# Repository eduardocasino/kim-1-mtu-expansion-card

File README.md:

# KIM-1 Expansion Board for MTU Cards

## About

Welcome to my KIM-1 Expansion Board for MTU cards repository.

This board follows the MTU standard for the KIM-1 expansion bus and enables to connect up to five cards, like the [K-1008](https://github.com/eduardocasino/k-1008-visable-memory-card-replica). Additionally, all signals of the KIM-1 are replicated on an edge connector to allow further expansions and also on a pin header for easy breadboarding.

The MTU bus connects 1 to 1 to the KIM-1 expansion connector with the exception of pins 2,3, 16, 17, 18, 19, 20 and X, because MTU boards use some of these pins for power and expanded 18 bit address bus (See page 33 of the [MTU Fall 1980 6502 Peripherals and Software catalog](http://retro.hansotten.nl/uploads/files/MTU-fall-1980.pdf)) Two pin connectors have to be wired to pins J (K7) and K (DECODE ENABLE) of the KIM-1 application connector.

Like in the original MTU's bus motherboard, a five screw terminal block provides power connectios for both the KIM-1 (GND, +5V and +12V regulated) and the expansion boards (+7.5V and +16V unregulated). Also as in the original, the +12V terminal is not really connected to anything.

This is how an example setup with one K-1008 board would look like:

The board has been built and tested with my [KIM-1](https://github.com/eduardocasino/kim-1) and [K-1008](https://github.com/eduardocasino/k-1008-visable-memory-card-replica) replicas.

## Licensing

This is a personal project that I am sharing in case it is of interest to any retrocomputing enthusiast and all the information in this repository is provided "as is", without warranty of any kind. I am not liable for any damages that may occur, whether it be to individuals, objects, KIM-1 computers, kittens or any other pets.

This work is licensed under a [Creative Commons Attribution-ShareAlike 4.0 International License](http://creativecommons.org/licenses/by-sa/4.0/).

See the LICENSE.md file for details.

## Changelog
#### 19/11/2023
* License change to a less restrictive one.
#### 11/11/2023
* Fix solder mask for connectors. For real this time. Damn.
#### 04/08/2023
* Fix solder mask for connectors

## Acknowledgements

* Hans Otten and his [Retro Computing blog](http://retro.hansotten.nl/). Documentation of MTU's line of hardware expansions for the KIM-1

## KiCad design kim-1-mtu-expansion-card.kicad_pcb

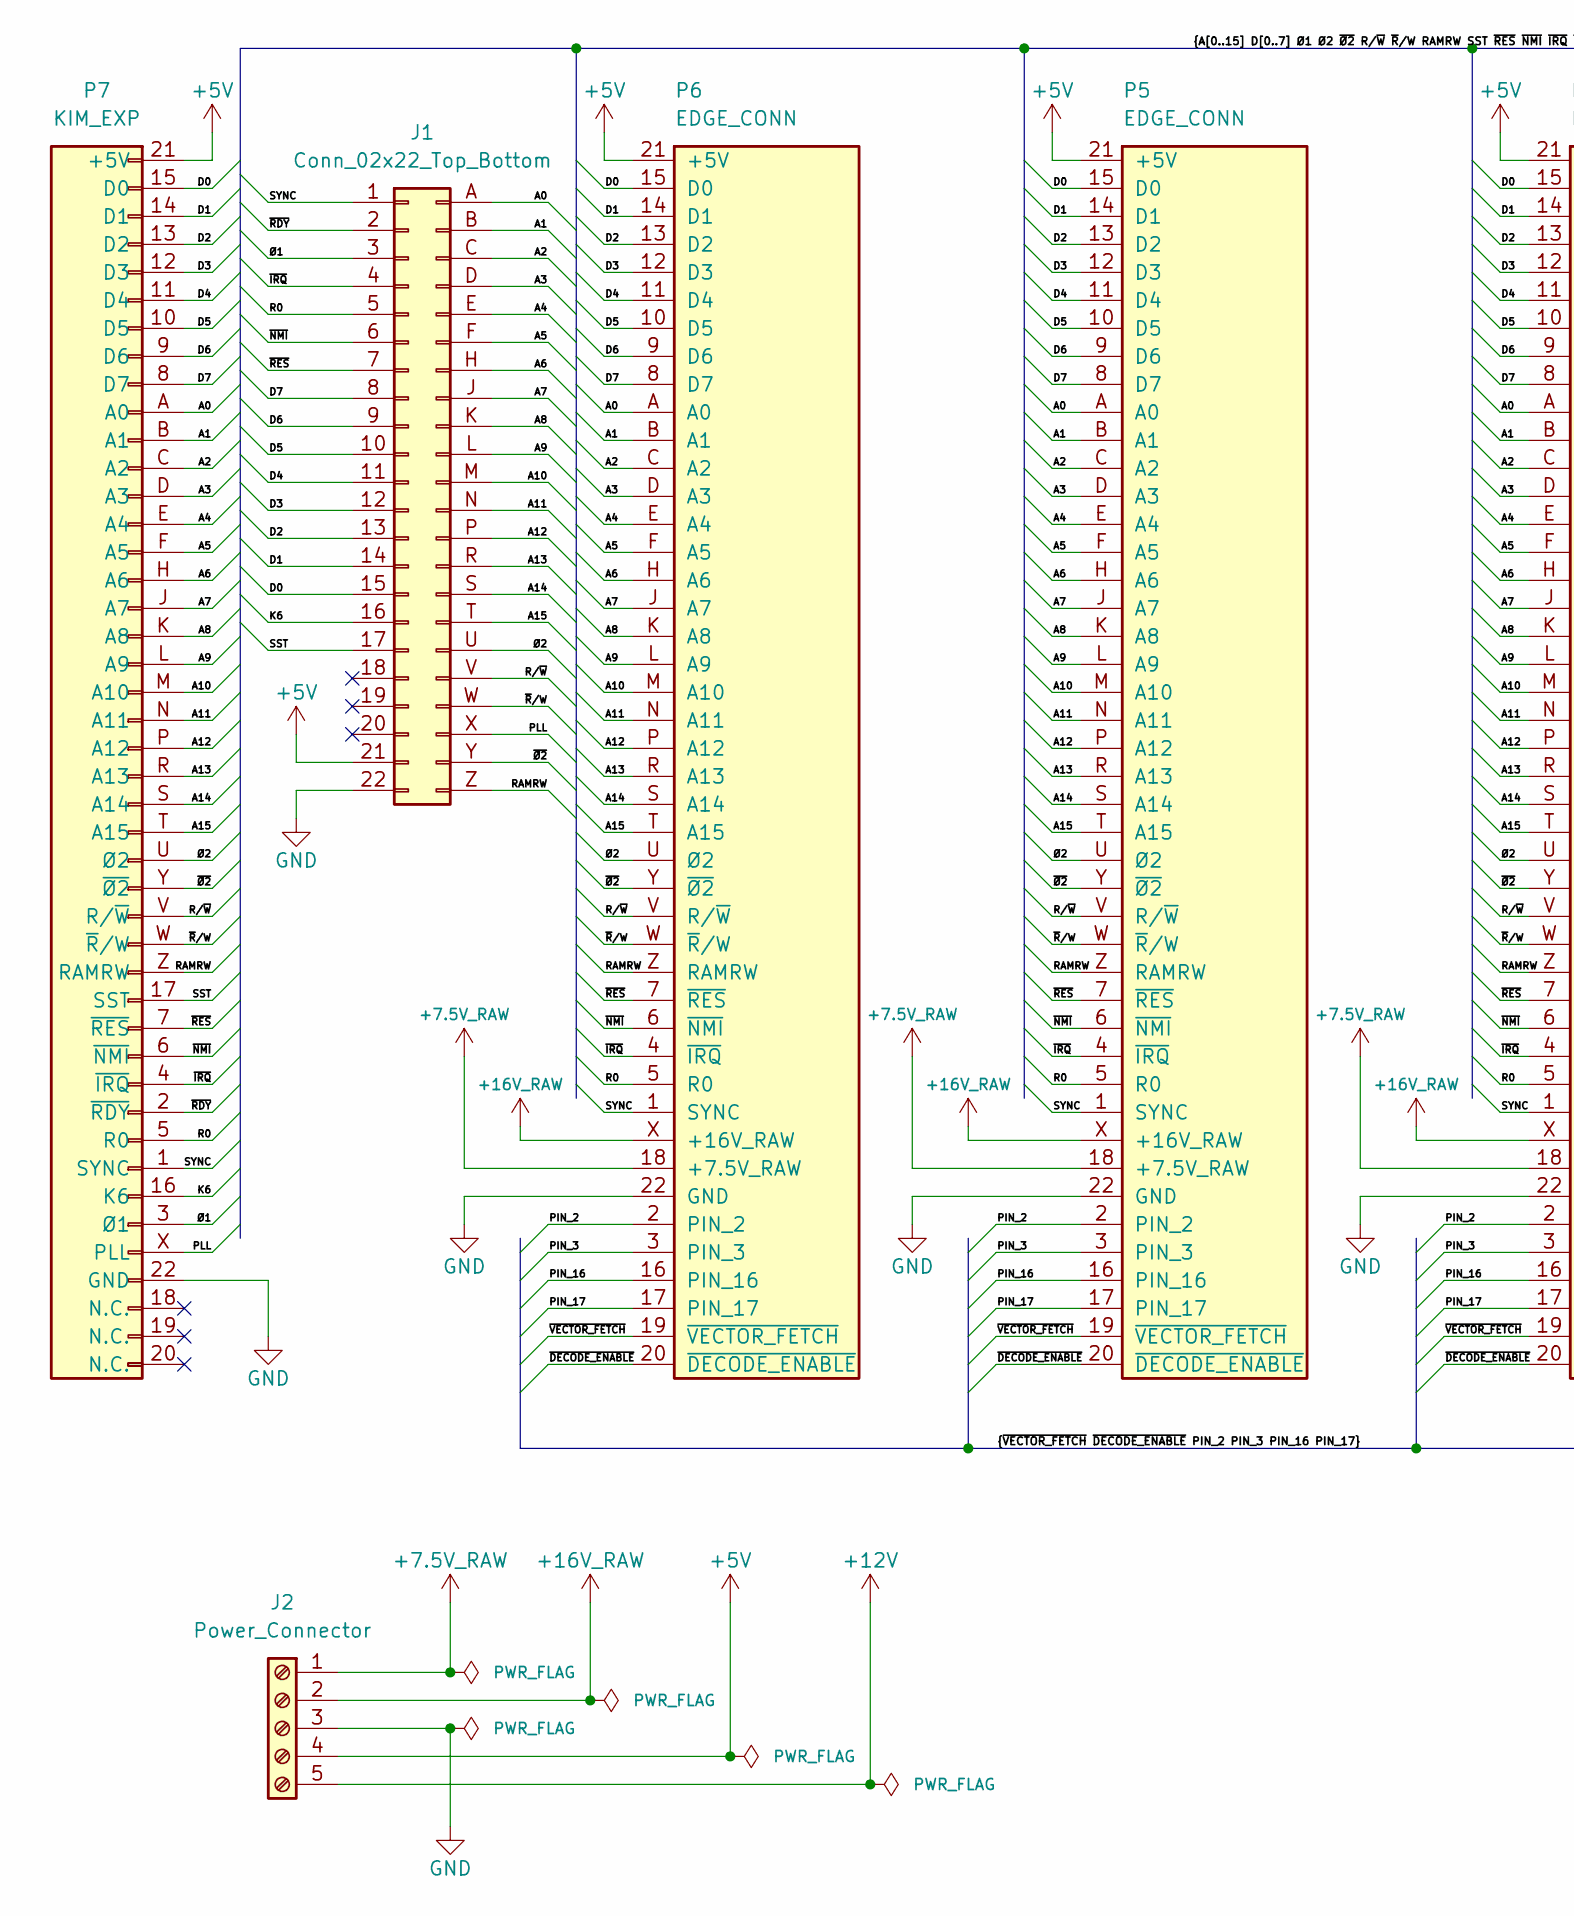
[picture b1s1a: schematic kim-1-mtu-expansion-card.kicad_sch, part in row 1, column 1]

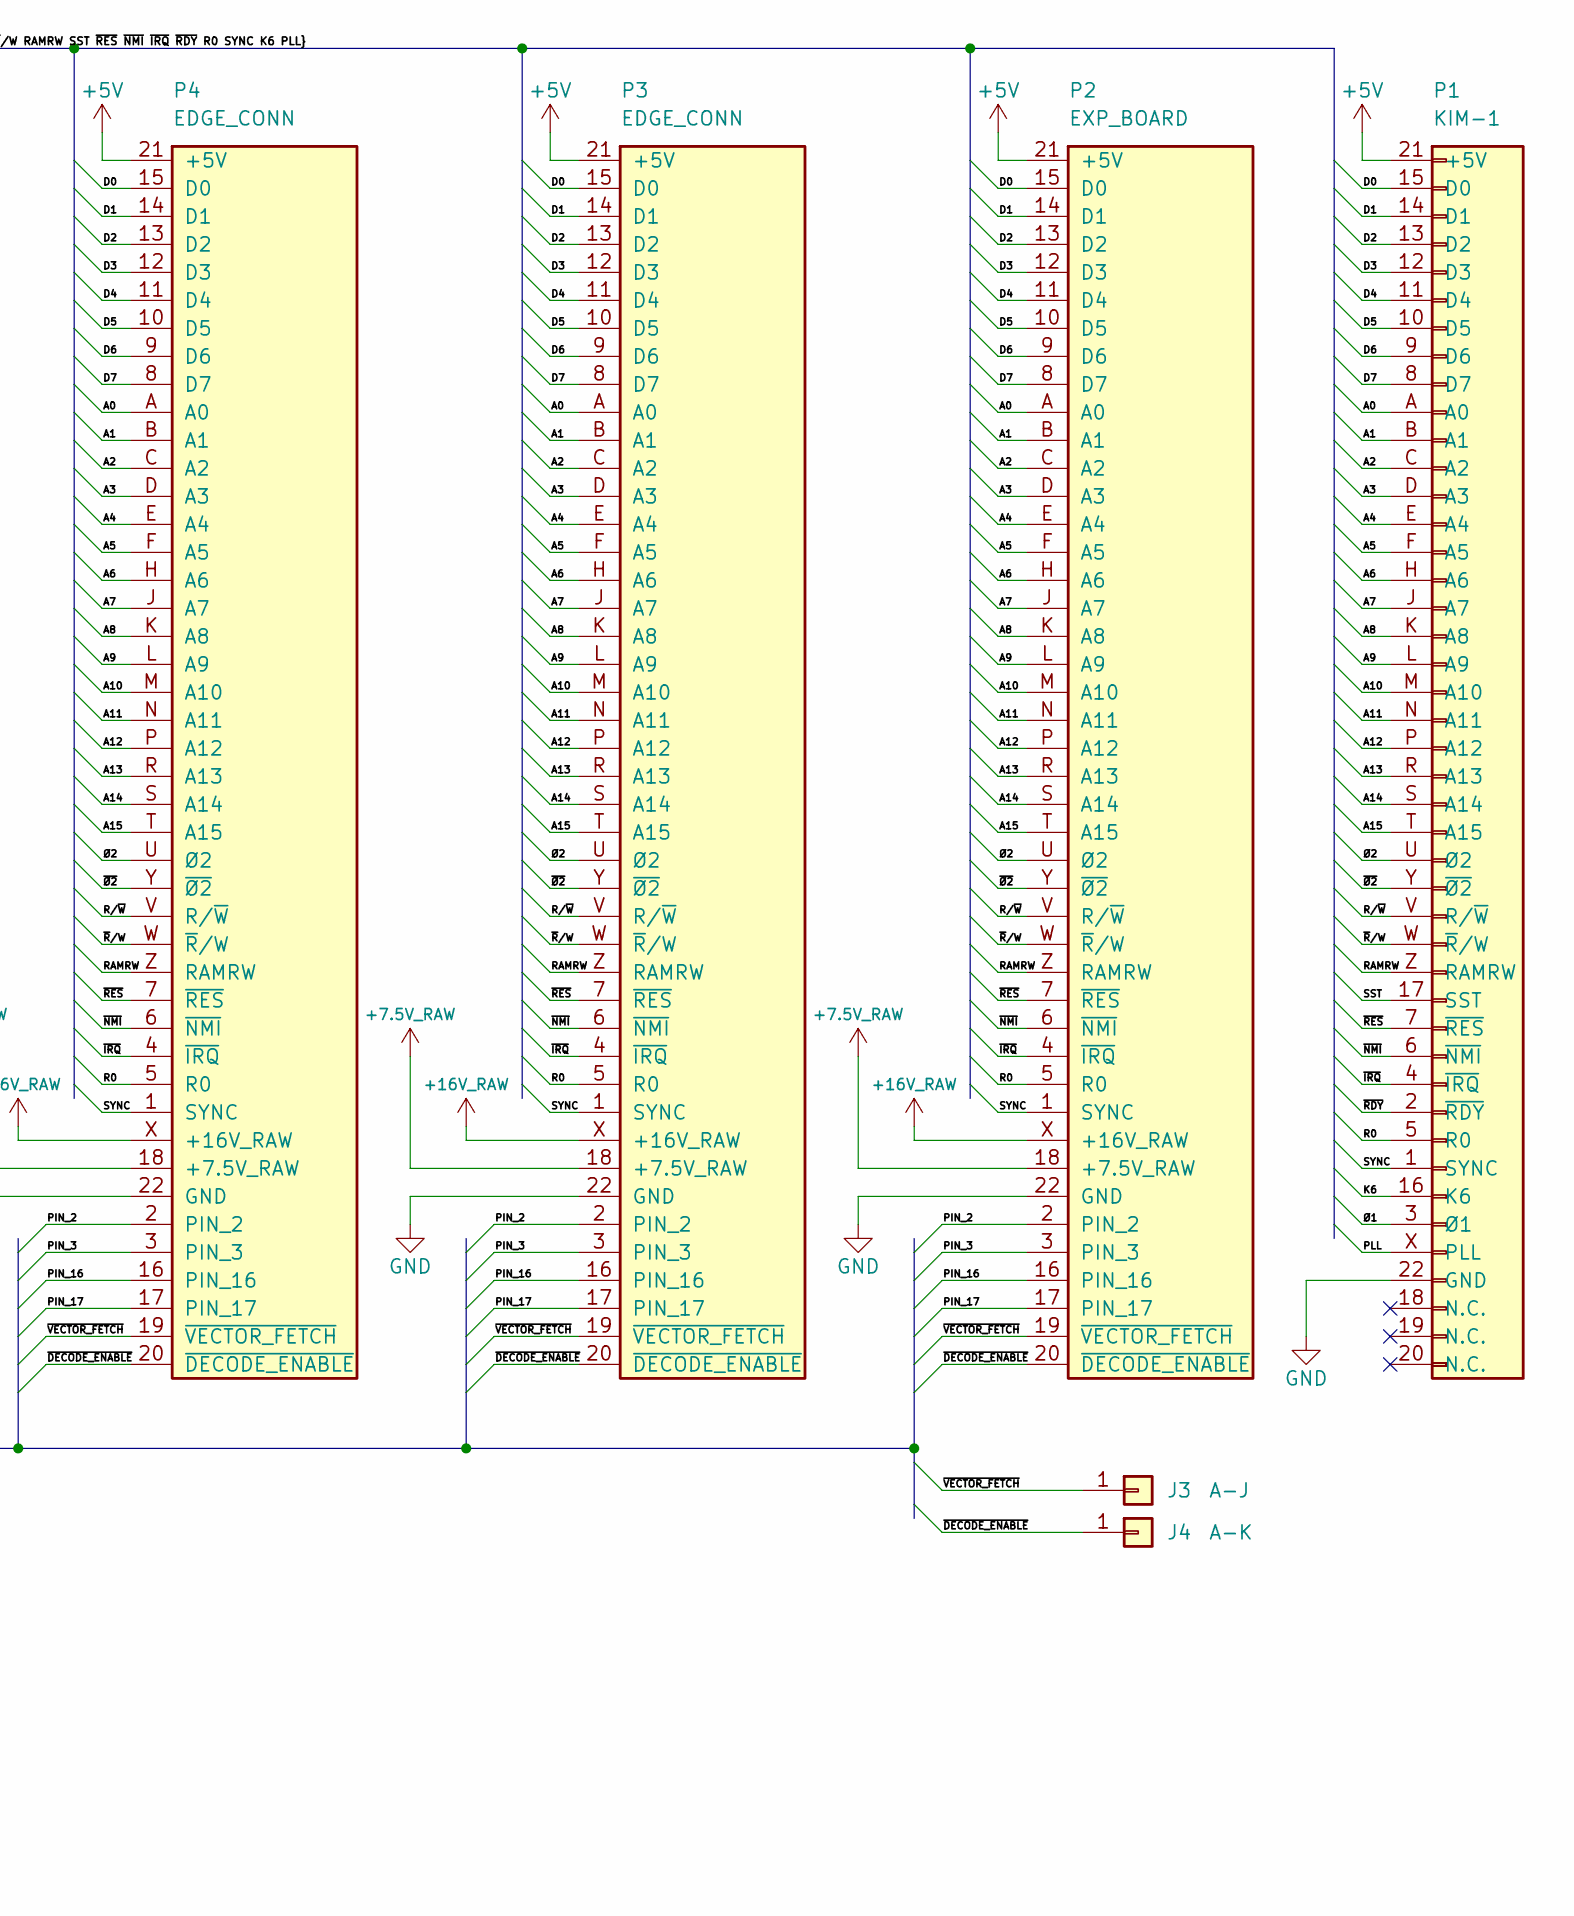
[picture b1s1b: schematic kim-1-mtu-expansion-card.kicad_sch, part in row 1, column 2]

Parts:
J1: Conn_02x22_Top_Bottom; PinHeader_2x22_P2.54mm_Vertical
J2: Power_Connector; TerminalBlock_Phoenix_MKDS-1,5-5_1x05_P5.00mm_Horizontal
J3: A-J; PinHeader_1x01_P2.54mm_Vertical
J4: A-K; PinHeader_1x01_P2.54mm_Vertical
P1: KIM-1; KIM_EDGE
P2: EXP_BOARD; EDAC-3.96-2x22
P3, P4, P5, P6: EDGE_CONN; EDAC-3.96-2x22
P7: KIM_EXP; KIM_CONN

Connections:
+5V: J1.21, J2.4, P1.21 (+5V), P2.21 (+5V), P3.21 (+5V), P4.21 (+5V), P5.21 (+5V), P6.21 (+5V), P7.21 (+5V)
+7.5V_RAW: J2.1, P2.18 (+7.5V_RAW), P3.18 (+7.5V_RAW), P4.18 (+7.5V_RAW), P5.18 (+7.5V_RAW), P6.18 (+7.5V_RAW)
+12V: J2.5
+16V_RAW: J2.2, P2.X (+16V_RAW), P3.X (+16V_RAW), P4.X (+16V_RAW), P5.X (+16V_RAW), P6.X (+16V_RAW)
/A0: J1.A, P1.A (A0), P2.A (A0), P3.A (A0), P4.A (A0), P5.A (A0), P6.A (A0), P7.A (A0)
/A1: J1.B, P1.B (A1), P2.B (A1), P3.B (A1), P4.B (A1), P5.B (A1), P6.B (A1), P7.B (A1)
/A2: J1.C, P1.C (A2), P2.C (A2), P3.C (A2), P4.C (A2), P5.C (A2), P6.C (A2), P7.C (A2)
/A3: J1.D, P1.D (A3), P2.D (A3), P3.D (A3), P4.D (A3), P5.D (A3), P6.D (A3), P7.D (A3)
/A4: J1.E, P1.E (A4), P2.E (A4), P3.E (A4), P4.E (A4), P5.E (A4), P6.E (A4), P7.E (A4)
/A5: J1.F, P1.F (A5), P2.F (A5), P3.F (A5), P4.F (A5), P5.F (A5), P6.F (A5), P7.F (A5)
/A6: J1.H, P1.H (A6), P2.H (A6), P3.H (A6), P4.H (A6), P5.H (A6), P6.H (A6), P7.H (A6)
/A7: J1.J, P1.J (A7), P2.J (A7), P3.J (A7), P4.J (A7), P5.J (A7), P6.J (A7), P7.J (A7)
/A8: J1.K, P1.K (A8), P2.K (A8), P3.K (A8), P4.K (A8), P5.K (A8), P6.K (A8), P7.K (A8)
/A9: J1.L, P1.L (A9), P2.L (A9), P3.L (A9), P4.L (A9), P5.L (A9), P6.L (A9), P7.L (A9)
/A10: J1.M, P1.M (A10), P2.M (A10), P3.M (A10), P4.M (A10), P5.M (A10), P6.M (A10), P7.M (A10)
/A11: J1.N, P1.N (A11), P2.N (A11), P3.N (A11), P4.N (A11), P5.N (A11), P6.N (A11), P7.N (A11)
/A12: J1.P, P1.P (A12), P2.P (A12), P3.P (A12), P4.P (A12), P5.P (A12), P6.P (A12), P7.P (A12)
/A13: J1.R, P1.R (A13), P2.R (A13), P3.R (A13), P4.R (A13), P5.R (A13), P6.R (A13), P7.R (A13)
/A14: J1.S, P1.S (A14), P2.S (A14), P3.S (A14), P4.S (A14), P5.S (A14), P6.S (A14), P7.S (A14)
/A15: J1.T, P1.T (A15), P2.T (A15), P3.T (A15), P4.T (A15), P5.T (A15), P6.T (A15), P7.T (A15)
/D0: J1.15, P1.15 (D0), P2.15 (D0), P3.15 (D0), P4.15 (D0), P5.15 (D0), P6.15 (D0), P7.15 (D0)
/D1: J1.14, P1.14 (D1), P2.14 (D1), P3.14 (D1), P4.14 (D1), P5.14 (D1), P6.14 (D1), P7.14 (D1)
/D2: J1.13, P1.13 (D2), P2.13 (D2), P3.13 (D2), P4.13 (D2), P5.13 (D2), P6.13 (D2), P7.13 (D2)
/D3: J1.12, P1.12 (D3), P2.12 (D3), P3.12 (D3), P4.12 (D3), P5.12 (D3), P6.12 (D3), P7.12 (D3)
/D4: J1.11, P1.11 (D4), P2.11 (D4), P3.11 (D4), P4.11 (D4), P5.11 (D4), P6.11 (D4), P7.11 (D4)
/D5: J1.10, P1.10 (D5), P2.10 (D5), P3.10 (D5), P4.10 (D5), P5.10 (D5), P6.10 (D5), P7.10 (D5)
/D6: J1.9, P1.9 (D6), P2.9 (D6), P3.9 (D6), P4.9 (D6), P5.9 (D6), P6.9 (D6), P7.9 (D6)
/D7: J1.8, P1.8 (D7), P2.8 (D7), P3.8 (D7), P4.8 (D7), P5.8 (D7), P6.8 (D7), P7.8 (D7)
/K6: J1.16, P1.16 (K6), P7.16 (K6)
/PIN_2: P2.2 (PIN_2), P3.2 (PIN_2), P4.2 (PIN_2), P5.2 (PIN_2), P6.2 (PIN_2)
/PIN_3: P2.3 (PIN_3), P3.3 (PIN_3), P4.3 (PIN_3), P5.3 (PIN_3), P6.3 (PIN_3)
/PIN_16: P2.16 (PIN_16), P3.16 (PIN_16), P4.16 (PIN_16), P5.16 (PIN_16), P6.16 (PIN_16)
/PIN_17: P2.17 (PIN_17), P3.17 (PIN_17), P4.17 (PIN_17), P5.17 (PIN_17), P6.17 (PIN_17)
/PLL: J1.X, P1.X (PLL), P7.X (PLL)
/R0: J1.5, P1.5 (R0), P2.5 (R0), P3.5 (R0), P4.5 (R0), P5.5 (R0), P6.5 (R0), P7.5 (R0)
/RAMRW: J1.Z, P1.Z (RAMRW), P2.Z (RAMRW), P3.Z (RAMRW), P4.Z (RAMRW), P5.Z (RAMRW), P6.Z (RAMRW), P7.Z (RAMRW)
/R/~W: J1.V, P1.V (R/~W), P2.V (R/~W), P3.V (R/~W), P4.V (R/~W), P5.V (R/~W), P6.V (R/~W), P7.V (R/~W)
/SST: J1.17, P1.17 (SST), P7.17 (SST)
/SYNC: J1.1, P1.1 (SYNC), P2.1 (SYNC), P3.1 (SYNC), P4.1 (SYNC), P5.1 (SYNC), P6.1 (SYNC), P7.1 (SYNC)
/~DECODE_ENABLE: J4.1, P2.20 (~DECODE_ENABLE), P3.20 (~DECODE_ENABLE), P4.20 (~DECODE_ENABLE), P5.20 (~DECODE_ENABLE), P6.20 (~DECODE_ENABLE)
/~IRQ: J1.4, P1.4 (~IRQ), P2.4 (~IRQ), P3.4 (~IRQ), P4.4 (~IRQ), P5.4 (~IRQ), P6.4 (~IRQ), P7.4 (~IRQ)
/~NMI: J1.6, P1.6 (~NMI), P2.6 (~NMI), P3.6 (~NMI), P4.6 (~NMI), P5.6 (~NMI), P6.6 (~NMI), P7.6 (~NMI)
/~RDY: J1.2, P1.2 (~RDY), P7.2 (~RDY)
/~RES: J1.7, P1.7 (~RES), P2.7 (~RES), P3.7 (~RES), P4.7 (~RES), P5.7 (~RES), P6.7 (~RES), P7.7 (~RES)
/~R/W: J1.W, P1.W (~R/W), P2.W (~R/W), P3.W (~R/W), P4.W (~R/W), P5.W (~R/W), P6.W (~R/W), P7.W (~R/W)
/~VECTOR_FETCH: J3.1, P2.19 (~VECTOR_FETCH), P3.19 (~VECTOR_FETCH), P4.19 (~VECTOR_FETCH), P5.19 (~VECTOR_FETCH), P6.19 (~VECTOR_FETCH)
/~Ø2: J1.Y, P1.Y (~Ø2), P2.Y (~Ø2), P3.Y (~Ø2), P4.Y (~Ø2), P5.Y (~Ø2), P6.Y (~Ø2), P7.Y (~Ø2)
/Ø1: J1.3, P1.3 (Ø1), P7.3 (Ø1)
/Ø2: J1.U, P1.U (Ø2), P2.U (Ø2), P3.U (Ø2), P4.U (Ø2), P5.U (Ø2), P6.U (Ø2), P7.U (Ø2)
GND: J1.22, J2.3, P1.22 (GND), P2.22 (GND), P3.22 (GND), P4.22 (GND), P5.22 (GND), P6.22 (GND), P7.22 (GND)

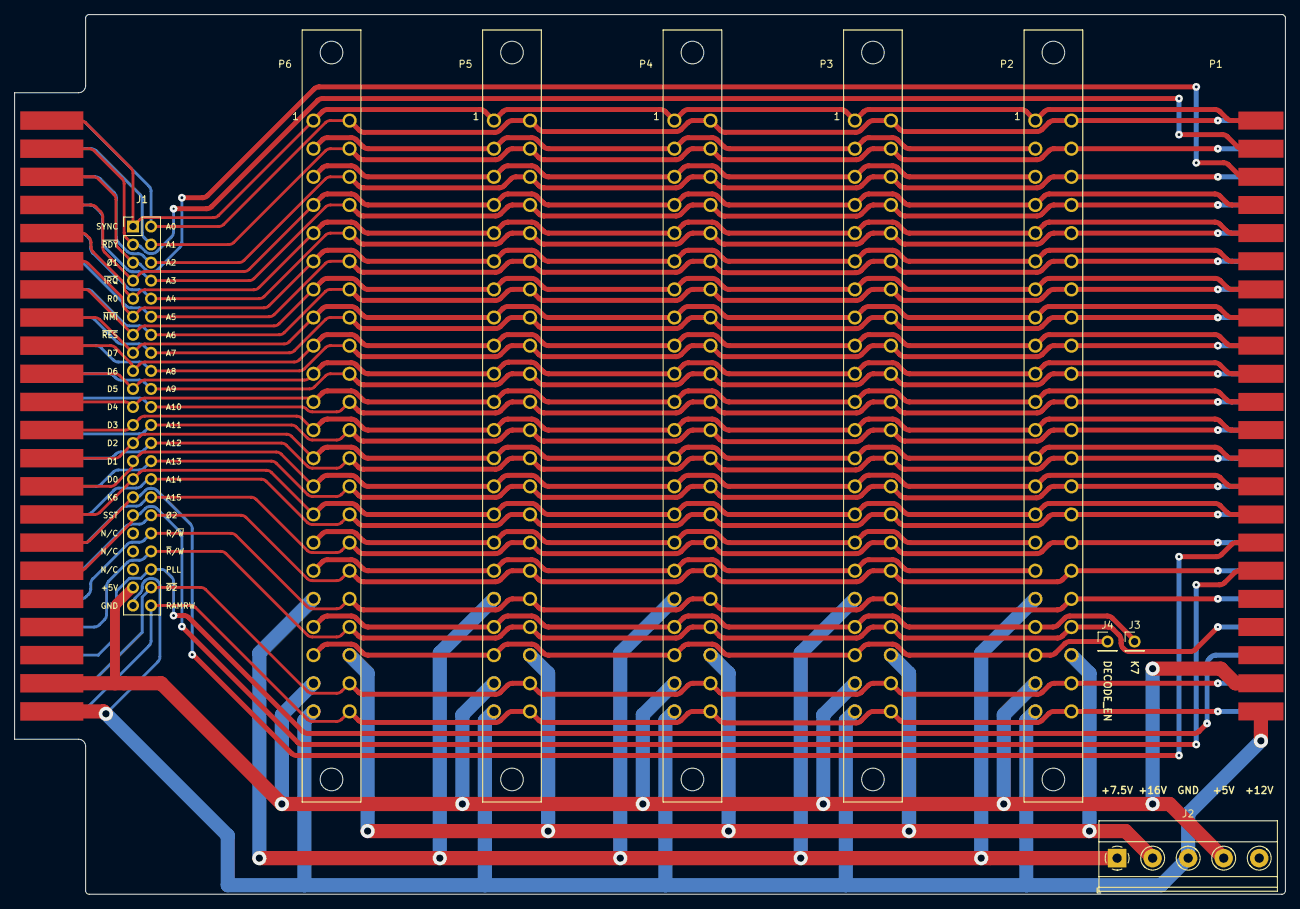
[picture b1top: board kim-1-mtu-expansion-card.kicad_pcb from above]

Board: 2 copper layers, 178.9 x 123.8 mm, 11 parts (0 on the bottom side), 49 nets.

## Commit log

2023-07-16 Thicker +5V track to pin header
2023-08-03 Fix solder mask for connectors
2023-08-17 Update status
2023-11-11 Fix solder mask. For real this time.
2023-11-19 Change license to CC-BY-SA
